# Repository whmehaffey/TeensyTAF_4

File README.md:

# TeensyTAF 4
Teensy v4 (pjrc.com)
https://www.pjrc.com/store/teensy40.html
and Teensy 4 Audio Shield
https://www.pjrc.com/store/teensy3_audio.html

with a small 100hz-(10-20)khz microphone based Target Audio Feedback (TAF) system. 
https://www.digikey.com/en/products/detail/cui-devices/CMEJ-4618-42-L010/10253438

Interface PCB @
https://oshpark.com/shared_projects/7dglGlFl

Parts list for Interface PCB is in .xls file included.

You will also need a stereo audio card- if your computer is mono, there are stereo USB cards available.
such as:
https://www.amazon.com/StarTech-com-Sound-SPDIF-Digital-Stereo/dp/B00F7120TQ/
or
https://www.amazon.com/VAlinks-External-Surround-Recording-Compatible/dp/B075F5VYG7/

Includes python GUI. 

Using:
pyserial
pyaudio (use https://www.lfd.uci.edu/~gohlke/pythonlibs/#pyaudio	with ALSA support. )
PyQtGraph
numpy

PyQt5 (use GUIQt5)

pip -m install pyqt5

Without the PCB, 

Basically, wire up the audio output jack with the Audio Channel (Left from the Teensy Audio Shield) going to the left channel, Pin 9 on the Teensy going to the right, and the audio ground (next to the Left channel) going to the ground pin.
Then, for another (preferably mono, but you could also just just one (or both) channels of a stereo jack) audio jack, run the 'Right' channel off the audio shield to your amplifier.
Once you have that, plug the audio channel into the Line-In on the USB sound card, and see if you see sound (once you've uploaded the sketch to the Teensy).
I often use Audacity for this (https://www.audacityteam.org/) because you can stream audio live and see how it looks either as an oscillogram, or as a spectrogram. 

Either way you'll need to attach a microphone to Mic-In on the Teensy Audio Shield, something like:
https://www.digikey.com/en/products/detail/cui-devices/CMEJ-4618-42-L010/10253438
or
https://www.digikey.com/en/products/detail/cui-devices/CMC-6010-42L100/7398903

depending on species, since you may want higher than 10khz (or not)
From the original documentation of the orignal CBS (Catch Bird Singing, by David Perkel), 

"Also, I am not a programmer, so I don't want to hear complaints.  I know it
isn't written well.  However, I would love to hear suggestions, even things
that may seem obvious."

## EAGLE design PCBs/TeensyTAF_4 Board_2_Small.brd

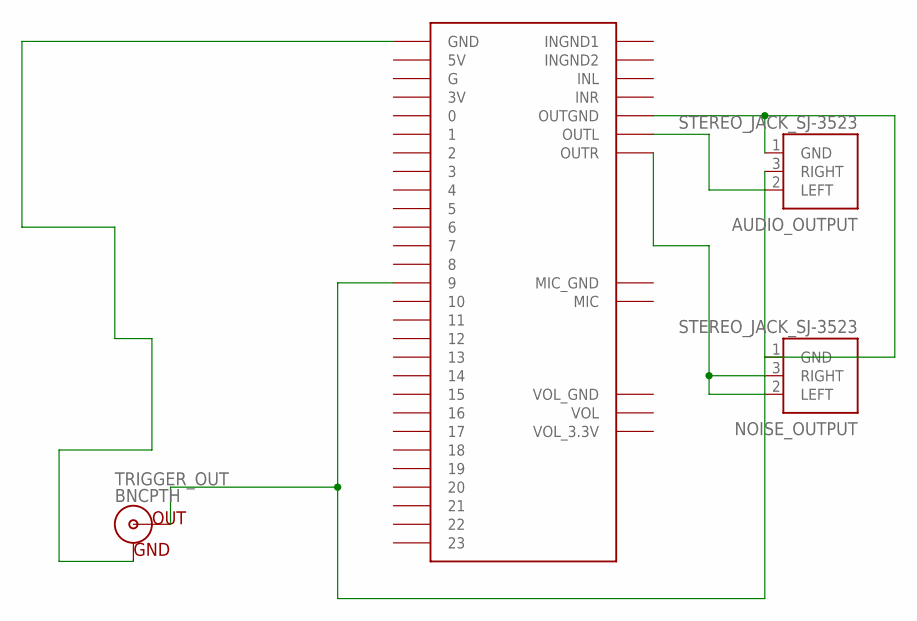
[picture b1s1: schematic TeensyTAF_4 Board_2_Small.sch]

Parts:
AUDIO_OUTPUT: STEREO_JACK_SJ-3523; SJ-3523
NOISE_OUTPUT: STEREO_JACK_SJ-3523; SJ-3523
TRIGGER_OUT: BNCPTH; BNC
U$3: AUDIOSHIELD

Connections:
unnamed: AUDIO_OUTPUT.3 (RIGHT), TRIGGER_OUT.S (OUT), U$3.9
unnamed: AUDIO_OUTPUT.2 (LEFT), U$3.OUTL
unnamed: NOISE_OUTPUT.2 (LEFT), NOISE_OUTPUT.3 (RIGHT), U$3.OUTR
unnamed: AUDIO_OUTPUT.1 (GND), NOISE_OUTPUT.1 (GND), U$3.OUTGND
unnamed: TRIGGER_OUT.GND, U$3.GND

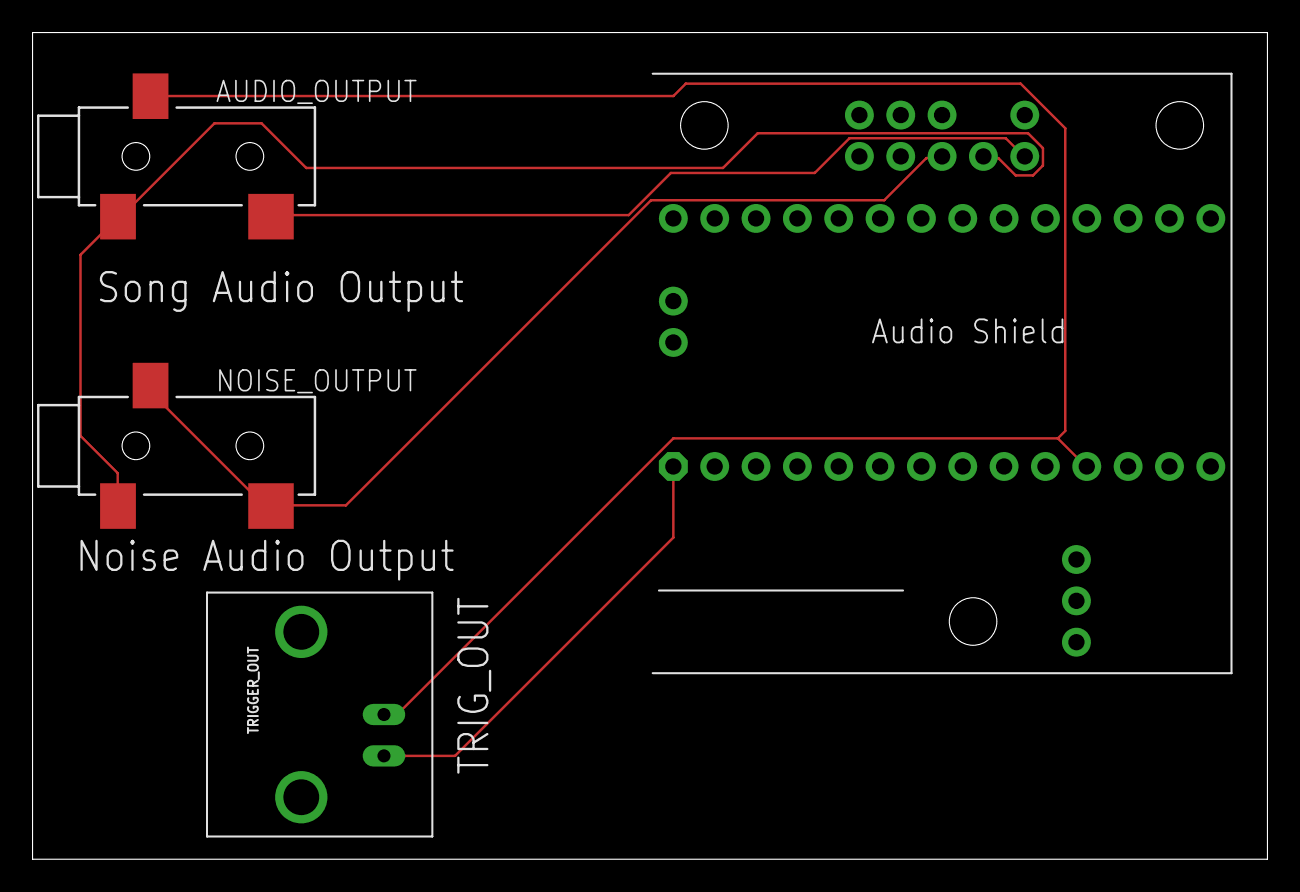
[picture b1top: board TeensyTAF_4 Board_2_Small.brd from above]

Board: 2 copper layers, 75.9 x 50.8 mm, 4 parts (0 on the bottom side), 5 nets.

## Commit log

2022-04-05 Qt5/QOL updates.
2022-04-12 Changed qProcessEvents, and fixed a type error in UpdateThreshold
2022-04-15 forced SpinBox to INT
2022-04-18 Fixed the defs for a 'too short' file (was scaling wrong with the buffer time)
2022-05-04 GUI fix and config file loading fix
2022-05-26 fixed buggs
    SavePath fixed, PreTemp spin box now updating values
2022-05-26 Update Gui.ui
    font size increased
    preTemp count max increased
2022-06-02 bug fix
2022-08-08 Removed Qt4 support
2022-09-14 Added PCBs
2022-09-14 Updates faster
2022-09-27 Updated PCBs
2022-11-03 Added 1024 point FFT and 22khz support
    Beta for 1024pt FFT and 22khz sampling rates

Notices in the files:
parts and their libraries:
SparkFun-Connectors: Licensing: Creative Commons ShareAlike 4.0 International - https://creativecommons.org/licenses/by-sa/4.0
